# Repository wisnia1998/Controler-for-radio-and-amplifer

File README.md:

# Controler-for-radio-and-amplifer
Controler for radio and amplifer

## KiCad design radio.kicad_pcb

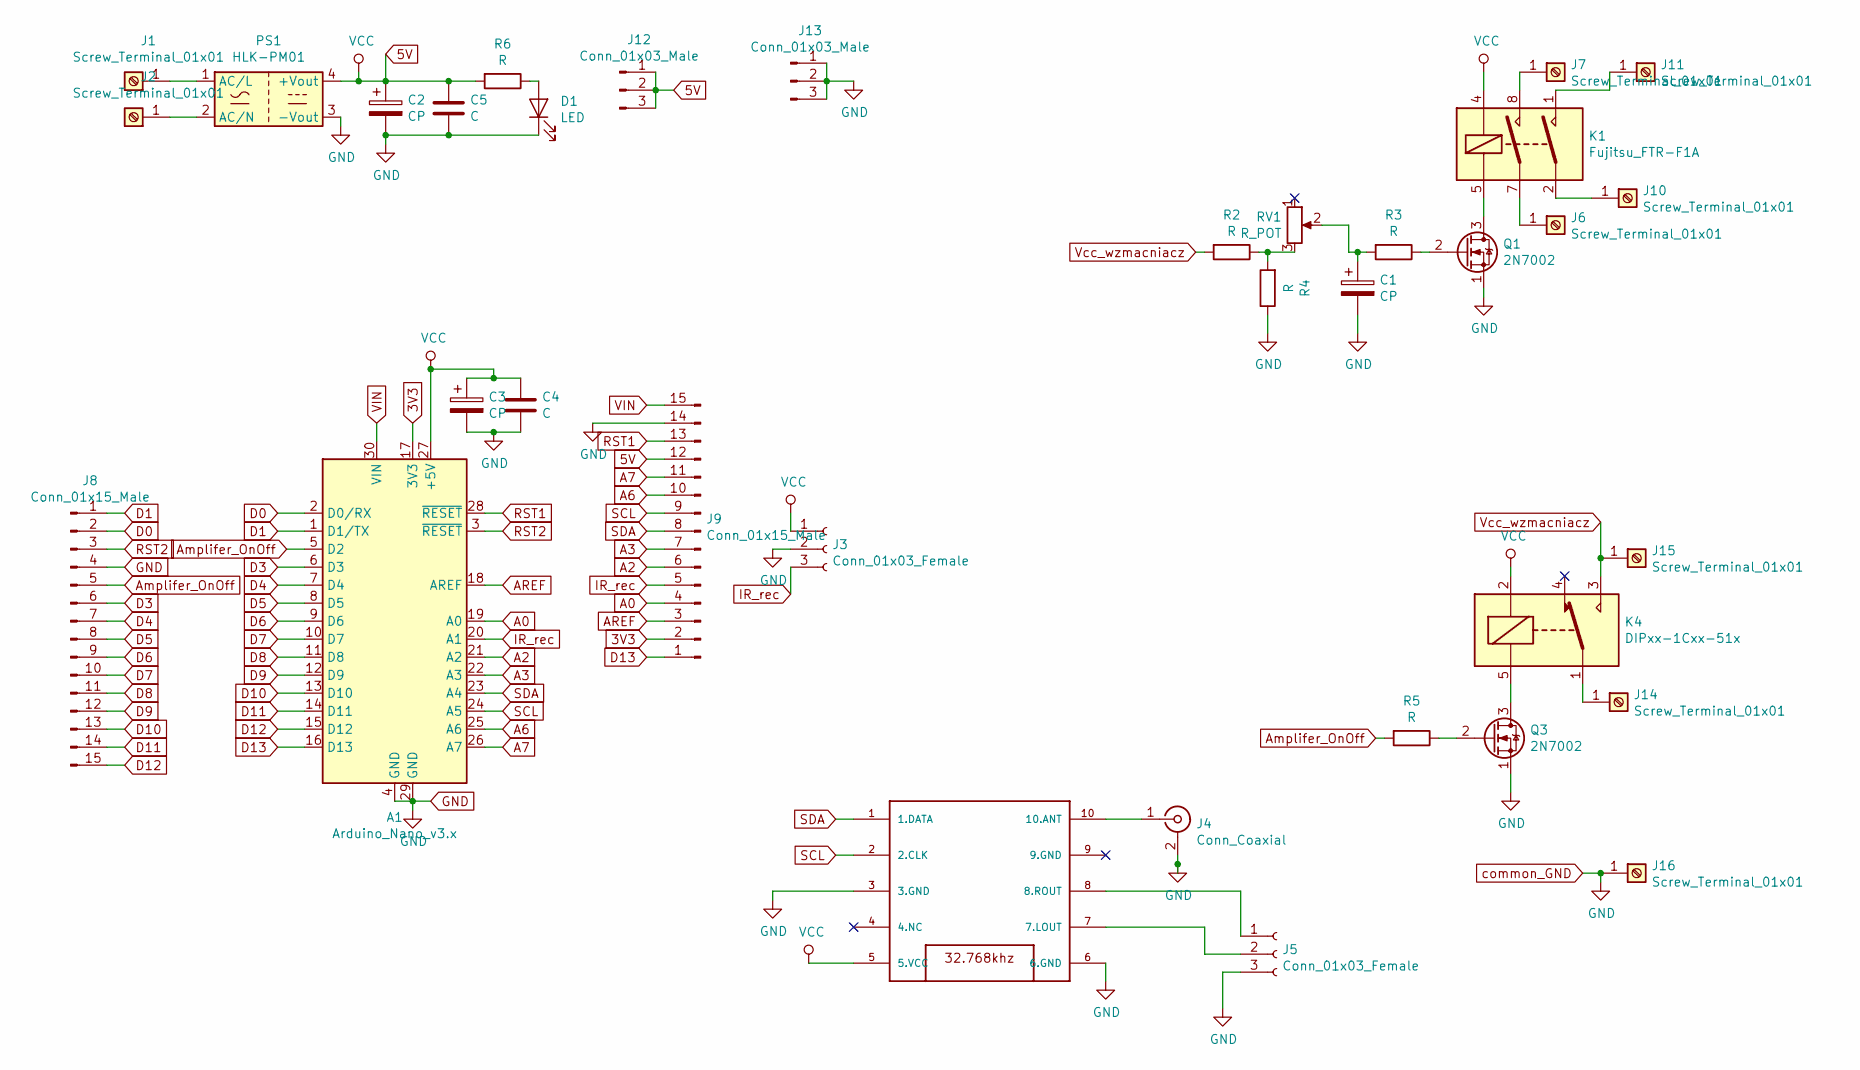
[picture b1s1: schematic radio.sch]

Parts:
A1: Arduino_Nano_v3.x; Arduino_Nano
C1, C2, C3: CP; CP_Radial_D4.0mm_P2.00mm
C4, C5: C; C_0805_2012Metric_Pad1.15x1.40mm_HandSolder
D1: LED; LED_0805_2012Metric_Pad1.15x1.40mm_HandSolder
J1, J2, J6, J7, J10, J11, J14, J15, J16: Screw_Terminal_01x01; SolderWirePad_1x01_Drill1.5mm
J3: Conn_01x03_Female; PinHeader_1x03_P1.00mm_Horizontal
J4: Conn_Coaxial; SMA_Amphenol_132291_Vertical
J5: Conn_01x03_Female; PinHeader_1x03_P1.00mm_Vertical
J8, J9: Conn_01x15_Male; PinHeader_1x15_P1.00mm_Vertical
J12, J13: Conn_01x03_Male; PinHeader_1x03_P1.00mm_Vertical
K1: Fujitsu_FTR-F1A; Relay_DPST_Fujitsu_FTR-F1A
K4: DIPxx-1Cxx-51x; Relay_SPDT_SANYOU_SRD_Series_Form_C
PS1: HLK-PM01; Converter_ACDC_HiLink_HLK-PMxx
Q1, Q3: 2N7002; TO-92L_Inline
R2, R3, R4, R5, R6: R; R_0805_2012Metric_Pad1.15x1.40mm_HandSolder
RV1: R_POT; Potentiometer_Bourns_3296W_Vertical
U1: TEA5767; TJ-102BC

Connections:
3V3: A1.17 (3V3), J9.2
5V: A1.27 (+5V), C2.1, C3.1, C4.1, C5.1, J3.1, J9.12, J12.1, J12.2, J12.3, K1.4, K4.2, PS1.4 (+Vout), R6.2, U1.5 (5.VCC)
A0: A1.19 (A0), J9.4
A2: A1.21 (A2), J9.6
A3: A1.22 (A3), J9.7
A6: A1.25 (A6), J9.10
A7: A1.26 (A7), J9.11
AREF: A1.18 (AREF), J9.3
Amplifer_OnOff: A1.5 (D2), J8.5, R5.2
D0: A1.2 (D0/RX), J8.2
D1: A1.1 (D1/TX), J8.1
D3: A1.6 (D3), J8.6
D4: A1.7 (D4), J8.7
D5: A1.8 (D5), J8.8
D6: A1.9 (D6), J8.9
D7: A1.10 (D7), J8.10
D8: A1.11 (D8), J8.11
D9: A1.12 (D9), J8.12
D10: A1.13 (D10), J8.13
D11: A1.14 (D11), J8.14
D12: A1.15 (D12), J8.15
D13: A1.16 (D13), J9.1
GND: A1.4 (GND), A1.29 (GND), C1.2, C2.2, C3.2, C4.2, C5.2, D1.1 (K), J3.2, J4.2 (Ext), J5.3, J8.4, J9.14, J13.1, J13.2, J13.3, J16.1, PS1.3 (-Vout), Q1.1 (S), Q3.1 (S), R4.1, U1.3 (3.GND), U1.6 (6.GND)
IR_rec: A1.20 (A1), J3.3, J9.5
unnamed: C1.1, R3.2, RV1.2
unnamed: D1.2 (A), R6.1
unnamed: J1.1, PS1.1 (AC/L)
unnamed: J2.1, PS1.2 (AC/N)
unnamed: J4.1 (In), U1.10 (10.ANT)
unnamed: J5.1, U1.8 (8.ROUT)
unnamed: J5.2, U1.7 (7.LOUT)
unnamed: J6.1, K1.7
unnamed: J7.1, K1.8
unnamed: J10.1, K1.2
unnamed: J11.1, K1.1
unnamed: J14.1, K4.1, K4.8
unnamed: K1.5, Q1.3 (D)
unnamed: K4.5, Q3.3 (D)
unnamed: Q1.2 (G), R3.1
unnamed: Q3.2 (G), R5.1
unnamed: R2.1, R4.2, RV1.3
RST1: A1.28 (~RESET), J9.13
RST2: A1.3 (~RESET), J8.3
SCL: A1.24 (A5), J9.9, U1.2 (2.CLK)
SDA: A1.23 (A4), J9.8, U1.1 (1.DATA)
VIN: A1.30 (VIN), J9.15
Vcc_wzmacniacz: J15.1, K4.3, R2.2

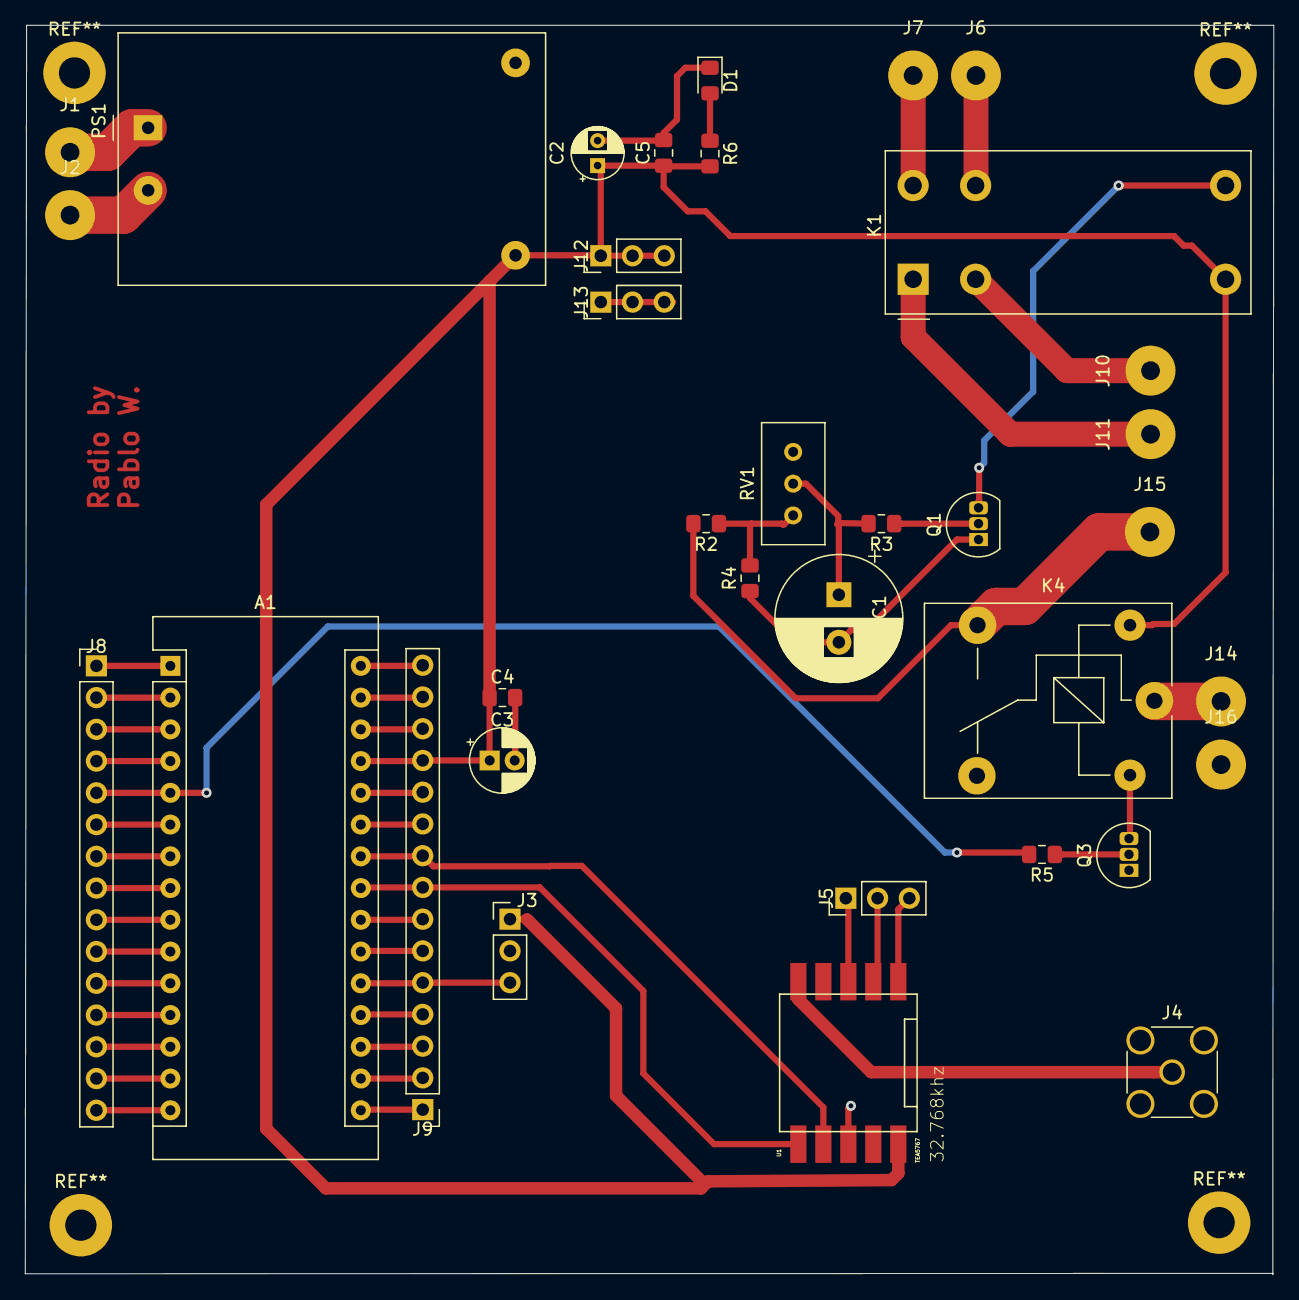
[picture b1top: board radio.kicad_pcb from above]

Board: 2 copper layers, 99.9 x 100.0 mm, 35 parts (0 on the bottom side), 47 nets.
